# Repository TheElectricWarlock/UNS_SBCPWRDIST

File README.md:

# Undernet Systems Single Board Computer Power Distribution
These are the design files for a DIY power distribution board for Single Board Computers powered by an ATX PSU. This board was designed to supply 5V to up to 6 Single Board Computers. An ATX power supply is used as the main source of power. 

This design contains the following features:
<ul>
<li>6 USB A ports.</li>
<li>Up to 4A per USB port.</li>
<li>Compatible with most ATX power supplies.</li>
<li>Decoupling Capacitance for each port.</li>
<li>Optional JST connections for each port. </li>
<li>Optional external power switch input for each port. </li>
<li>Optional motor driver circuitry for cooling fan control (PWM controlled). </li>
</ul>

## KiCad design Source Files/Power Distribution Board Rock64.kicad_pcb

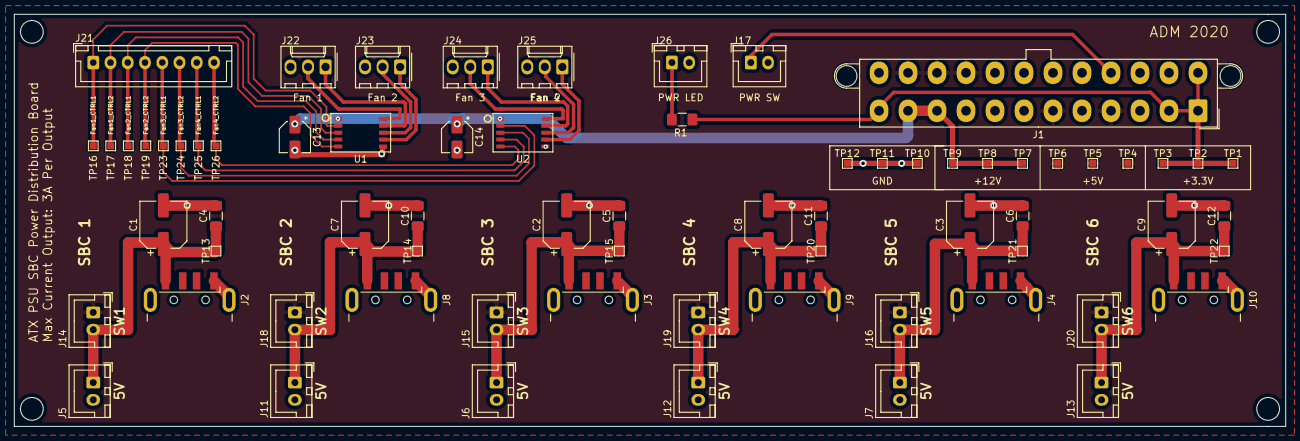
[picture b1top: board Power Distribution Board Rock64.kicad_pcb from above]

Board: 2 copper layers, 184.2 x 59.7 mm, 69 parts (0 on the bottom side), 28 nets.

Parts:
C1, C2, C3, C7, C8, C9: 47uF; CP_Elec_6.3x5.4
C4, C5, C6, C10, C11, C12: 100nF; C_1206_3216Metric_Pad1.42x1.75mm_HandSolder
C13, C14: 10uF; CP_Elec_4x5.4
J1: 442060007; Molex_Mini-Fit_Jr_5566-24A2_2x12_P4.20mm_Vertical
J2, J3, J4, J8, J9, J10: 87583-3010RPALF; USB_A_CNCTech_1001-011-01101_Horizontal_Fixed
J5, J6, J7, J11, J12, J13, J14, J15, J16, J17, J18, J19, J20, J26: XHP-2; JST_XH_B2B-XH-A_1x02_P2.50mm_Vertical
J21: B8B-XH-A(LF)(SN); JST_XH_B8B-XH-A_1x08_P2.50mm_Vertical
J22, J23, J24, J25: 22232031; Molex_KK-254_AE-6410-03A_1x03_P2.54mm_Vertical
R1: 300; R_1206_3216Metric_Pad1.42x1.75mm_HandSolder
TP1: 3V_TP1; TestPoint_Pad_1.0x1.0mm
TP2: 3V_TP2; TestPoint_Pad_1.0x1.0mm
TP3: 3V_TP3; TestPoint_Pad_1.0x1.0mm
TP4: 5V_TP1; TestPoint_Pad_1.0x1.0mm
TP5: 5V_TP2; TestPoint_Pad_1.0x1.0mm
TP6: 5V_TP3; TestPoint_Pad_1.0x1.0mm
TP7: 12V_TP1; TestPoint_Pad_1.0x1.0mm
TP8: 12V_TP2; TestPoint_Pad_1.0x1.0mm
TP9: 12V_TP3; TestPoint_Pad_1.0x1.0mm
TP10: GND_TP1; TestPoint_Pad_1.0x1.0mm
TP11: GND_TP2; TestPoint_Pad_1.0x1.0mm
TP12: GND_TP3; TestPoint_Pad_1.0x1.0mm
TP13: P5V_B1; TestPoint_Pad_1.0x1.0mm
TP14: P5V_B2; TestPoint_Pad_1.0x1.0mm
TP15: P5V_B3; TestPoint_Pad_1.0x1.0mm
TP16: F1_C1; TestPoint_Pad_1.0x1.0mm
TP17: F1_C2; TestPoint_Pad_1.0x1.0mm
TP18: F2_C1; TestPoint_Pad_1.0x1.0mm
TP19: F2_C2; TestPoint_Pad_1.0x1.0mm
TP20: P5V_B4; TestPoint_Pad_1.0x1.0mm
TP21: P5V_B5; TestPoint_Pad_1.0x1.0mm
TP22: P5V_B6; TestPoint_Pad_1.0x1.0mm
TP23: F3_C1; TestPoint_Pad_1.0x1.0mm
TP24: F3_C2; TestPoint_Pad_1.0x1.0mm
TP25: F4_C1; TestPoint_Pad_1.0x1.0mm
TP26: F4_C2; TestPoint_Pad_1.0x1.0mm
U1, U2: LV8548MC; SOIC-10

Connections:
+3.3V: J1.1, J1.2, J1.12, J1.13, R1.2, TP1.1, TP2.1, TP3.1
+5V: J1.4, J1.6, J1.21, J1.22, J1.23, J14.1, J15.1, J16.1, J18.1, J19.1, J20.1, TP4.1, TP5.1, TP6.1
+12V: C13.1, C14.1, J1.10, J1.11, TP7.1, TP8.1, TP9.1, U1.1, U2.1
Fan1_CTRL1: J21.1, TP16.1, U1.2
Fan1_CTRL2: J21.2, TP17.1, U1.3
Fan2_CTRL1: J21.3, TP18.1, U1.4
Fan2_CTRL2: J21.4, TP19.1, U1.5
Fan3_CTRL1: J21.5, TP23.1, U2.2
Fan3_CTRL2: J21.6, TP24.1, U2.3
Fan4_CTRL1: J21.7, TP25.1, U2.4
Fan4_CTRL2: J21.8, TP26.1, U2.5
GND: C1.2, C2.2, C3.2, C4.2, C5.2, C6.2, C7.2, C8.2, C9.2, C10.2, C11.2, C12.2, C13.2, C14.2, J1.3, J1.5, J1.7, J1.15, J1.17, J1.18, J1.19, J1.24, J2.4, J2.5, J3.4, J3.5, J4.4, J4.5, J5.2, J6.2, J7.2, J8.4, J8.5, J9.4, J9.5, J10.4, J10.5, J11.2, J12.2, J13.2, J17.2, J26.2, TP10.1, TP11.1, TP12.1, U1.6, U2.6
unnamed: J22.1, U1.9
unnamed: J22.2, U1.10
unnamed: J23.1, U1.7
unnamed: J23.2, U1.8
unnamed: J24.1, U2.9
unnamed: J24.2, U2.10
unnamed: J25.1, U2.7
unnamed: J25.2, U2.8
unnamed: J26.1, R1.1
P5V_1: C1.1, C4.1, J2.1, J5.1, J14.2, TP13.1
P5V_2: C7.1, C10.1, J8.1, J11.1, J18.2, TP14.1
P5V_3: C2.1, C5.1, J3.1, J6.1, J15.2, TP15.1
P5V_4: C8.1, C11.1, J9.1, J12.1, J19.2, TP20.1
P5V_5: C3.1, C6.1, J4.1, J7.1, J16.2, TP21.1
P5V_6: C9.1, C12.1, J10.1, J13.1, J20.2, TP22.1
PS-ON: J1.16, J17.1

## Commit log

2021-09-08 Initial commit of design files
2021-09-08 Updated project description
2021-09-08 Fixed typos
